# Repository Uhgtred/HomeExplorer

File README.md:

# HomeExplorer

Robotproject mostly for learning about robotics myself. Documentation is going to be updated, as soon as there is a version that I am satisfied with.

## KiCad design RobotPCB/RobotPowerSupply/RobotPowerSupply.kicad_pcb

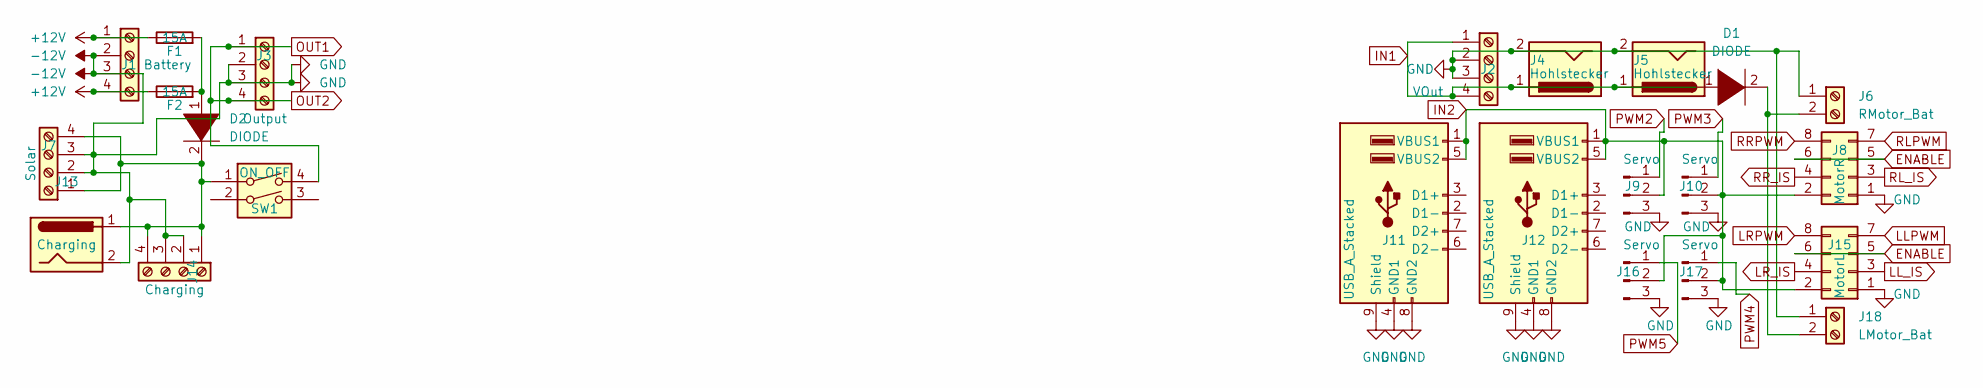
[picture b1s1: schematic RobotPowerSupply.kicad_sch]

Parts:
D1, D2: DIODE; D_1812_4532Metric_Pad1.30x3.40mm_HandSolder
F1, F2: 15A; Fuseholder_Cylinder-6.3x32mm_Schurter_0031-8002_Horizontal_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
J1: Battery; TerminalBlock_bornier-4_P5.08mm
J2: VOut; TerminalBlock_bornier-4_P5.08mm
J3: Output; TerminalBlock_bornier-4_P5.08mm
J4, J5: Hohlstecker; BarrelJack_Horizontal
J6: RMotor_Bat; TerminalBlock_bornier-2_P5.08mm
J7: Solar; TerminalBlock_bornier-4_P5.08mm
J8: MotorR; PinSocket_2x04_P2.54mm_Vertical_SMD
J9, J10, J16, J17: Servo; PinHeader_1x03_P2.54mm_Vertical_SMD_Pin1Right
J11, J12: USB_A_Stacked; USB_A_Wuerth_61400826021_Horizontal_Stacked
J13: Charging; BarrelJack_Horizontal
J14: Charging; TerminalBlock_bornier-4_P5.08mm
J15: MotorL; PinSocket_2x04_P2.54mm_Vertical_SMD
J18: LMotor_Bat; TerminalBlock_bornier-2_P5.08mm
SW1: ON_OFF; SW_DIP_SPSTx01_Slide_6.7x4.1mm_W6.73mm_P2.54mm_LowProfile_J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

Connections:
+12V: F1.1, F2.1, J1.1, J1.4
-12V: J1.2, J1.3, J2.2, J2.3, J3.2, J3.3, J4.2, J5.2, J6.1, J7.2, J7.3, J8.1, J9.3, J10.3, J11.4 (GND1), J11.8 (GND2), J11.9 (Shield), J12.4 (GND1), J12.8 (GND2), J12.9 (Shield), J13.2, J14.2, J14.3, J15.1, J16.3, J17.3, J18.1
ENABLE: J8.5, J8.6, J15.5, J15.6
IN1: D1.1 (K), J2.1, J2.4, J4.1, J5.1
IN2: J8.2, J9.2, J10.2, J11.1 (VBUS1), J11.5 (VBUS2), J12.1 (VBUS1), J12.5 (VBUS2), J15.2, J16.2, J17.2
LLPWM: J15.7
LL_IS: J15.3
LRPWM: J15.8
LR_IS: J15.4
unnamed: D1.2 (A), J6.2, J18.2
unnamed: D2.1 (K), F1.2, F2.2
unnamed: D2.2 (A), J7.1, J7.4, J13.1, J14.1, J14.4, SW1.1
OUT1: J3.1, J3.4, SW1.2, SW1.4
PWM2: J9.1
PWM3: J10.1
PWM4: J17.1
PWM5: J16.1
RLPWM: J8.7
RL_IS: J8.3
RRPWM: J8.8
RR_IS: J8.4

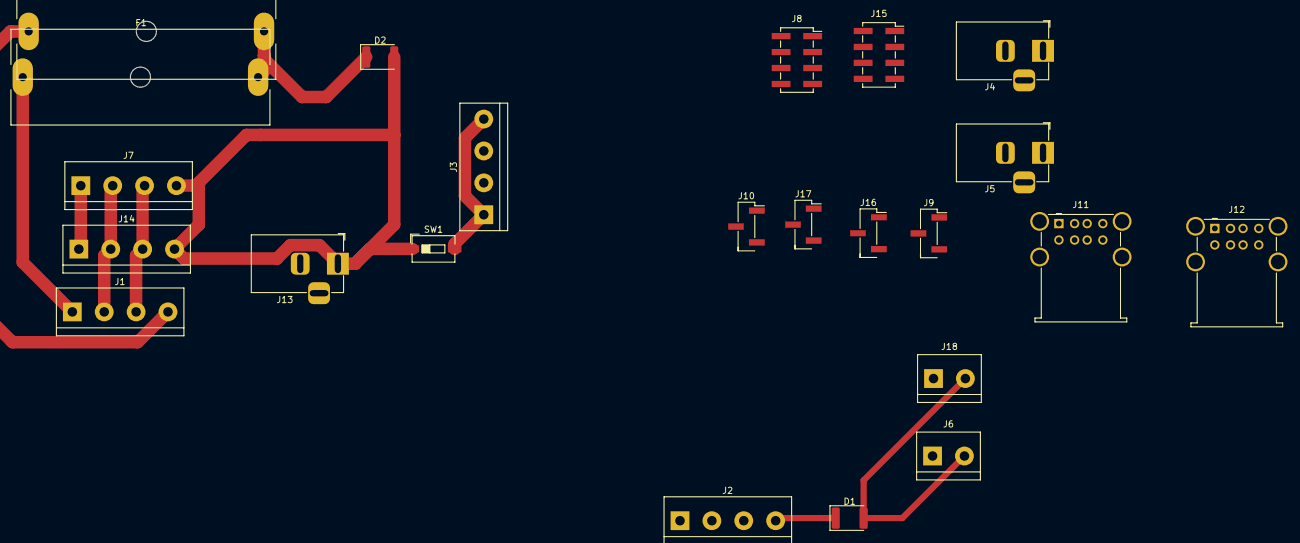
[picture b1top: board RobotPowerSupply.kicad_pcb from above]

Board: 2 copper layers, 23 parts (0 on the bottom side), 9 nets.

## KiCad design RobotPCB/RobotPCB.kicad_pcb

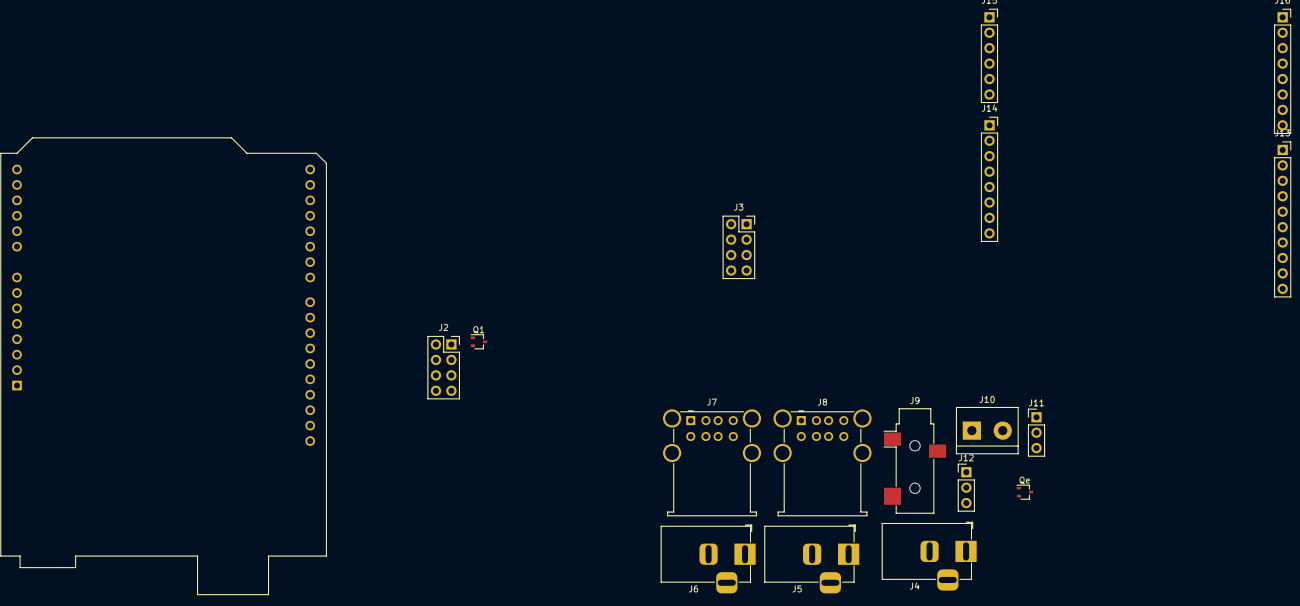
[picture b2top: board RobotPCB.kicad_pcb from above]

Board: 2 copper layers, 18 parts (0 on the bottom side), 18 nets, no tracks yet.

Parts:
A1: Arduino_UNO_R3
J2, J3: Conn_02x04_Top_Bottom; PinSocket_2x04_P2.54mm_Vertical
J4, J5, J6: Jack-DC; BarrelJack_Horizontal
J7, J8: USB_A_Stacked; USB_A_Wuerth_61400826021_Horizontal_Stacked
J9: AudioJack2_Ground; Jack_3.5mm_CUI_SJ-3523-SMT_Horizontal
J10: Screw_Terminal_01x02; TerminalBlock_bornier-2_P5.08mm
J11, J12: Conn_01x03_Male; PinHeader_1x03_P2.54mm_Vertical
J13: Conn_01x10_Male; PinSocket_1x10_P2.54mm_Vertical
J14, J16: Conn_01x08_Male; PinSocket_1x08_P2.54mm_Vertical
J15: Conn_01x06_Male; PinSocket_1x06_P2.54mm_Vertical
Q1: 2SC4213; SOT-323_SC-70
Qe: 2SC4213; SOT-323_SC-70

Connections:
+5V: A1.5 (+5V), J2.1, J3.1, J7.1 (VBUS1), J7.5 (VBUS2), J8.1 (VBUS1), J8.5 (VBUS2), J11.2, J12.2, Q1.3 (C), Qe.3 (C)
+12V: J4.1, J5.1, J6.1
-12V: J4.2, J5.2, J6.2
GND: A1.7 (GND), J2.5, J3.5, J7.4 (GND1), J7.8 (GND2), J7.9 (Shield), J8.4 (GND1), J8.8 (GND2), J8.9 (Shield), J11.3, J12.3
LPWML: A1.23 (D8), J2.8
LPWMR: A1.22 (D7), J2.4
L_EN: J2.7, J3.7
L_IS: J2.6, J3.6
unnamed: J9.S, Q1.2 (E)
unnamed: J9.T, Qe.2 (E)
unnamed: J10.1, Q1.1 (B)
unnamed: J10.2, Qe.1 (B)
RPWML: A1.19 (D4), J3.8
RPWMR: A1.17 (D2), J3.4
R_EN: J2.3, J3.3
R_IS: J2.2, J3.2
SERVOX: A1.20 (D5), J11.1
SERVOZ: A1.21 (D6), J12.1

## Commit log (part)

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2022-08-11 Initial Setup
2022-08-11 Deleting unnecessary data
2022-08-11 Cleaning code
2022-08-12 Changing some imports
2022-08-12 Making code mor modular and oop
2022-08-17 Adapting the Microcotroller-setting to arduino mega and reactivating servo-control
2022-08-19 A lot of Coderework especially in Network
2022-08-21 Network now working as should and nicely done
2022-08-22 Changing Board a little
2022-08-22 Last bugfix. Now network is working fine
2022-08-24 Improving code and throwing out unnecessary config-entries
2022-08-24 Slight improvement to ConfigReader and removing line-breaks, which I dont like
2022-08-24 Improveing code for Arduino-communication
2022-08-25 Feature/voltage measurement (#16)
    * First attempt of implementing voltage-measurement on the arduino
    * Improveing code for Arduino-communication
    * Returned to original code, since it was running and I have other things to do
2022-08-26 Improvements/general code improvements (#18)
    * Improving code and throwing out unnecessary config-entries
    * Restructured the main-programs to make them more modular and readable. Put securtity-parameter to shutdown motors if errors in communication
    * Slight improvement to ConfigReader and removing line-breaks, which I dont like
2022-08-26 Tried to go on, but too fatique
2022-09-10 Final adaptions to System, should be running with working microcontroller
2023-02-26 Pushing the new version that has been developed locally
2023-02-26 removing some unncessary code and comments
2023-02-27 Switching from QT-framework to tkinter since code is more readable
2023-03-04 GUI-Videostream working fluently but with very low resolution only. Next Steps: 1. Find out what is taking the most time. 2. improve the part that takes the most time (multiprocessing, cython, splitt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
2023-03-07 Reworking the controller-class
2023-03-08 Reactivating Servo-functionality and solving few bugs
2023-03-08 Adding comments to Camera-module
2023-03-08 Optimizing the imports.
2023-03-09 Adapting all remaining imports to the new import-system + deleting unused imports
2023-03-09 Removing unnecessary variable-declaration Putting some comments
2023-03-12 Improvement/imports (#38)
    * Reworking the controller-class
    * Reworking the controller-class + depending modules
    * Reactivating Servo-functionality and solving few bugs
    * Optimizing the imports.
    * Adapting all remaining imports to the new import-system + deleting unused imports
2023-03-12 Fixed some bugs Partly fell back to old architecture because the performance was not good enough and the event-based system is bad for controlling the robot (e.g connection-loss could lead the robot 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
2023-03-18 Reworking the Arduino code, to make the serial-connection as stable as possible
2023-03-25 Improving the readybility of the arduino code bugfixing
2023-03-26 Fixing small but important bug
2023-03-27 Changing the value of memset
2023-04-03 Initial commit of Threadmanager (untested and not implemented)
2023-04-18 Reworking the SocketMessenger-code and documenting it with comments
2023-07-01 Architecture-draft for the camera module. Restructuring code according to this draft
2024-01-28 Camera-Module
    Build a modular Camera-Module inside a Video-package. No unit-tests until now
2024-01-30 Video-feature
2024-01-30 Protocol instead abstract class
    decided that a protocol is a better solution in this case then an abstract class
2024-01-31 understanding opencv in c++
2024-02-01 unit-test
    camera unit-tests done
2024-02-04 python not too slow!
    Python module was working fast enough. The camera says it has 30 fps when in reality it only gives me 17. c++ code gave me the same amount of fps
2024-02-04 Moving camera from class-var to instance-var
    Moving camera-variable from class to instance so its possible to instance multiple cameras
2024-02-04 further implementation
    Further implementing the video-module
2024-02-06 structure
2024-02-07 starting automated unit-testing
2024-02-07 switching directories
2024-02-11 Switching directories (#43)
    * switching directories
    * numpy and bytesio wont work together
    sadly it is not possible to get numpy.save working with bytesio, so i have to search for another solution probably going for simple file. If this is too slow, maybe have to switch to c++
    * Update SerializationNumpySave.py
    * Update main.yml
    * Update Dockerfile
2024-02-12 Implement start and stop methods in VideoController class
    - Added start method to begin video capture and transmission
    - Continuous frame acquisition, serialization, and transmission implemented in start method
    - Added stop method to end video capture and transmission
    - Class attributes protected and state-controlled through is_running flag
2024-02-12 Update Video_Architecture.drawio
    system with 2 threads needs to be finished inside the sequence-diagram
2024-02-13 updating github actions
2024-02-13 stub for camera-module
    stub for videocamera and removing files with old naming, where the refactoring of pycharm copied them instead of renaming the original files
2024-02-13 applying architecture
2024-02-13 adapting unit-tests
2024-02-13 Update VideoCamera.py
    removing comments that where lines from an older version of this file
2024-02-13 utilizing runners
2024-02-13 Update main.yml
    cleaning out old code which is no longer needed
2024-02-21 minor corrections in bustransactions
2024-02-29 start implementing main.py
2024-02-29 Update Tcp_Udp_sockets.py
    chose a set instead of a list. Operating with a set is faster
2024-02-29 Optimizing code
    Adding typehints where they have been missing so far.
2024-02-29 starting with exception-handling
2024-02-29 returning from set to list partially
    in iterative attempts sets are not a good idea, since they do not allow a modification during runtime
2024-02-29 Bugfix in asyncRunner and VideoCamera
2024-02-29 adapting port of the api
2024-03-01 implementing unit-tests
2024-03-01 adding an argument to the api
2024-03-02 modularizing unit-tests
2024-03-12 updating BusTransactions
2024-03-12 done
2024-03-17 wild tests
2024-03-18 Update testImage
2024-03-20 renaming module
2024-03-22 bugfixing and structural changes
    still need to do unit-tests for this and for the steeringdevice-stuff on the other side.
2024-03-23 update actorcontrol
2024-03-24 Thinking of other architectorial ways to solve this
2024-03-25 further implementation of the architecture
2024-03-26 fixing a bug with name-mangeling
2024-03-28 update architecture
    Updating the architecture and adapting the code.
2024-03-29 adaption of unit-test
2024-03-29 suggesting a better architecture
2024-03-30 Bugfix for unit-test
2024-03-31 bugfixing serialbus unittests
2024-04-04 Implementing the new reworked architectrure
    Adapting unit-tests
    Stabilizing code
    start Error-handling
2024-04-06 using protocol instead of abstract class
2024-04-10 making a mapping for the controller-values
2024-08-06 Update RobotController.ino
    removing an unnecessary allocation
2024-09-01 Update to the EventManager.py
    Eventmanager now has the possibility to subscribe to a specified Event.
2024-09-11 small adaption
2024-09-28 Introducing clientIpAddress to udp-config
    The ip-address in the udp-config has not been sufficient to manage every task. That is why after some system-tests now the variable clientIpAddress has been introduced to the udp-config
2024-10-07 Added a todo.
2024-10-21 switch to json
    for encoding switched to json instead of pickle, because pickle is very unsecure in terms of executable code in objects
2024-10-24 debug-lines added
2024-10-25 communication working now!
2024-10-27 arduino-code is running
2025-01-06 Refactor motor control logic and fix motor direction bug
    Removed unused code in the loop function to declutter and improve readability. Corrected calls to `SetRightMotorsZero` and `SetLeftMotorsZero` to fix the motor direction handling bug. Added a TODO co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
2025-01-17 Enable servo control and clean up motor control logic.
    Re-enabled the ServoControl function call in the main loop for motor and servo coordination. Removed commented-out testing code and deprecated motor control logic to improve readability and maintaina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
2025-01-23 Refactor FPS handling and improve system initialization.
    Updated FPS calculation to handle negative values safely and renamed setter parameter for clarity. Enhanced initialization process with additional logging and moved some asynchronous tasks to thread-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
2025-02-01 Refactor serialization interface and implementations.
    Updated `SerializerInterface` to use a unified `serialize` method with support for both image data and file paths. Refactored all serializer implementations to align with this new interface, ensuring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
2025-02-03 Refactor serialization and transmission to use MsgPack.
    Replaced Joblib-based serialization with MsgPack for improved efficiency and compatibility. Updated related methods, interfaces, and factories accordingly, and marked unused Joblib code as deprecated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
2025-02-05 implementation of CompressorInterface.py and CompressorZlib.py for support of compression of video-data
2025-02-07 implementing logging
2025-02-07 Refactor video processing to improve modularity and clarity
    Updated video frame processing to adjust the compression and serialization order. Replaced direct instantiations with factory methods for better encapsulation. Improved logging, corrected method defi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
2025-02-11 Update Dockerfile to use Ubuntu 22.04 and streamline installs
    Set a specific base image (Ubuntu 22.04) to ensure consistency and compatibility. Combined apt commands into a single line with --no-install-recommends to reduce image size and improve build efficien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
2025-02-20 Refactor bus transceivers, logging, and socket handling.
    Refactored factories for serial and UDP transceivers, introducing clarity and modularization. Enhanced logging in video, event, and socket modules for better debug visibility. Updated requirements, s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
2025-02-20 Refactor camera setup to improve clarity and support flexibility.
    Renamed variables in `__setupCamera` to improve readability and added support for additional arguments in `VideoCameraStub`. This enhances code maintainability and allows for more versatile camera in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
2025-03-14 utilizing an enum for input-device-type
2025-03-14 deploy: 0583da2819fa6f7a637aae1e7090cc7bca0b22c6
2025-03-16 Simplify debug logging in ActorControlFactory.
    Condensed redundant debug log messages in `createActorController` to improve clarity and reduce verbosity. This ensures logs remain focused while still providing necessary information.
2025-03-20 Enhance Event class with verbose logging and interface implementation
    Implemented the EventInterface in the Event class and added a verbose logging mechanism for subscriber notifications. Replaced the set with a WeakSet for managing subscribers to improve memory handli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
2025-03-20 Remove EventInterface and update Event class accordingly
    The EventInterface abstraction was deemed unnecessary and has been removed to simplify the codebase. The Event class was updated to work independently without relying on the removed interface. This c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
2025-03-21 Add MkDocs configuration for project documentation
    Introduced a basic MkDocs configuration with a Material theme to structure project documentation. Added navigation entries for Home, Features, and Setup sections to provide an organized overview of t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
2025-04-05 Refactor logging and motor control logic
    Enhanced the Logger class with improved configuration capabilities, consistent formatting, and comprehensive documentation. Modified Arduino motor control logic by introducing zeroing methods for bet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
2025-05-09 updating the bustransactions
2025-05-12 Update GitHub Actions to use latest action versions
    Upgraded actions/checkout, actions/upload-artifact, and peaceiris/actions-gh-pages to their latest major versions. This ensures compatibility with the latest features and security updates for the wor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
2025-12-12 Optimization of produceEvent in EventManager.py
2025-12-17 optimizations and cleaning code + introducing Encryption.py and EncryptionProtocol.py
2026-04-08 Shifting buttonconfig to remote + refactoring
2026-04-24 Updating main.yml so that the project is running with uv instead pip now.
